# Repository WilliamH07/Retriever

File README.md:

<div align="center">

# Retriever

**Open source autonomous outdoor mobile robot**

[Architecture](docs/architecture/) ·
[Getting started](docs/DEMARRAGE.md) ·
[Bench reports](docs/bancs/) ·
[Hardware](hardware/) ·
[Support the project](#supporting-the-project)

</div>

---

## What this is

Retriever is a four wheel drive outdoor robot, built by one person and released
as open hardware. Its single objective is autonomous outdoor navigation with
ROS 2 Jazzy and Nav2, on a chassis anyone can reproduce from documented,
commodity parts.

It is an open rebuild inspired by the [Clearpath
Husky](https://clearpathrobotics.com/husky-a300-unmanned-ground-vehicle-robot/),
a reference platform in mobile robotics labs. The Husky is an excellent machine,
priced as a commercial product. Retriever asks a different question: how much of
that capability can one person reach from recovered and off the shelf parts, if
the engineering is done properly rather than cheaply?

The hardware is deliberately ordinary. The discipline applied to it is not: an
architecture dossier written before the first part was cut, a failure mode
analysis, a hardware safety chain no software can override, and a measurable
exit criterion at every stage.

## Status

<div align="center">

</div>

| Stage | Exit criterion | State |
|:-----:|----------------|-------|
| 1 | Architecture dossier and CAD complete | done |
| 2 | Chassis fabricated and assembled | done |
| 2b | First sensors published to ROS 2 over a transport agnostic link | done: [IMU](docs/bancs/imu.md) at 99.8 Hz, [lidar](docs/bancs/lidar.md) |
| 2c | Motor bench: hub motors driven from Foxglove | **current**: [coded, first spin due](docs/bancs/moteurs.md) |
| 3 | Three PCBs redesigned, power chain energised, no motor connected | **boards designed**: [KiCad, ERC and DRC clean](hardware/pcb/), fabrication next |
| 4 | Motors driven, wheels raised, all stop tests pass | planned |
| 5 | Autonomous outdoor navigation to a waypoint | planned |

Beyond stage 5, the plan is to mount a [Niryo
One](https://github.com/NiryoRobotics/niryo_one) arm and turn Retriever into a
mobile manipulator.

<div align="center">

</div>

## System architecture

<div align="center">

</div>

Three decisions shape everything else.

**A CAN bus, not USB, carries every command.** Four BLDC drivers chopping tens
of amps within 30 cm of the signal wiring make USB the wrong choice for the
control path: it is master slave, dynamically enumerated, with no frame
priority. CAN 2.0A at 500 kbit/s links the computer to every microcontroller.
USB is kept for high bandwidth perception, whose loss degrades the mission but
cannot cause dangerous motion. On the bench today the same frames travel over
serial; one Kconfig option and one launch parameter switch to CAN.

**The main computer never does real time.** It runs perception, localisation,
Nav2 and the mission, and produces setpoints. A dedicated safety
microcontroller decides whether they may be executed: the computer requests
arming, the safety node grants or refuses it.

**Safety is hardware, and independent of software.** Six stop levels, from a
100 ms software collision monitor down to a latching emergency stop and a
manual battery isolator. The last two contain no code at all.

<div align="center">

</div>

## Power

<div align="center">

</div>

The contactor is designed onto the power board rather than bought: a
`TPS48100-Q1` driving two opposed MOSFETs cuts a fault in 4.3 µs, draws 4 mW
instead of a coil's 2 to 8 W, and can test itself. The trade off is documented
in [`12-contacteur-statique.md`](docs/architecture/12-contacteur-statique.md).

## Printed circuit boards

<div align="center">

</div>

| Board | Role | State |
|---|---|---|
| [`safety_bus_distribution`](hardware/pcb/safety_bus_distribution/) | CAN and `/SAFE` trunk, protected 5 V per node, no microcontroller | **v2.0, ready to order** |
| [`motor_interface`](hardware/pcb/motor_interface/) | Hall tap and command path between a MOTION ESP32 and two ZS-X11H drivers | v2.0 draft, waits for motor measurements |
| [`safety_power`](hardware/pcb/safety_power/) | Battery input, static contactor, precharge, brake chopper, rails, SAFETY ESP32 | v2.0 draft, waits for pack measurements and an expert review |

Each board is described once, in a Python script that generates both the KiCad 10
schematic and the layout, so the two cannot drift apart. ERC, DRC and schematic
parity are all at zero, and the Gerber, BOM and placement files are committed.
The analogue blocks were simulated with ngspice, which caught one defect before
anything was ordered ([simulations](hardware/pcb/simulations.md)). None of the
boards has been built yet: [status of all three](hardware/pcb/etat-des-lieux.md)
(French).

## Hardware at a glance

| | |
|---|---|
| Configuration | 4WD skid steer, outdoor |
| Structure | Aluminium extrusion frame, laser cut panels, 3D printed mounts |
| Target mass | 35 kg in running order |
| Target speed | 1.5 m/s, slopes up to 10 % |
| Drivetrain | 4 × 6.5 inch hoverboard hub motors, 250 W each, 15 pole pairs |
| Motor drivers | 4 × ZS-X11H BLDC drivers, two per motor node |
| Battery | Xiaomi M365 Pro pack, 10S4P, 37 V nominal (30 to 42 V), 474 Wh |
| Endurance | about 2 h at 200 W average (estimate, 85 % depth of discharge) |
| Compute | Youyeetoo X1 (Celeron N5105), Ubuntu 24.04, ROS 2 Jazzy |
| Real time | 3 × ESP32 (SAFETY, MOTION front, MOTION rear) on CAN 2.0A, 500 kbit/s |
| Sensors | BNO085 IMU (SPI), YDLIDAR X4, GNSS; outdoor lidar and depth camera wanted |
| Localisation | GNSS, IMU and wheel odometry, dual EKF |
| Navigation | Nav2, collision monitor, twist mux |

## Repository layout

```
docs/
  architecture/   the design dossier: 00–07 base, 08–12 PCB and errata, 13 software
  bancs/          bench reports: IMU, lidar, motors (French)
  DEMARRAGE.md    getting started, from a blank machine to /imu/data (French)
  measurements/   bench measurements that gate the hardware design
  foxglove/       Foxglove Studio layouts for each bench
  images/         renders, build photos, diagrams
  sponsorship/    the sponsorship dossier
  archive/        superseded work, kept for history
hardware/
  icd.yaml        interface control document: every connector, every pin
  pcb/            three boards, generated from Python into KiCad 10, with fab files
  cad/            laser cut DXF profiles, mechanical notes
  bom/            pointer to the costed bill of materials
firmware/
  protocol/       protocol.yaml, the single source of truth, and its generator
  components/     link layer, protocol header, BNO085 driver
  esp32_safety/   safety node (IMU bench today)
  esp32_motion/   motor node, front and rear
  test/           host tests, no hardware needed
ros2_ws/src/
  retriever_link/       transport agnostic bridge: serial today, SocketCAN later
  retriever_protocol/   generated protocol header for ROS 2
  retriever_msgs/       message definitions
  retriever_bringup/    launch files and bench configurations
  retriever_*           description, hardware, control, navigation, teleop: planned
tools/            bench scripts, flashing, protocol and link checks
```

## Documentation

The design documentation is in French; an English summary is planned. Every
claim carries a marker: verified against a datasheet, community consensus, to
be measured, or an explicit assumption.

| Start with | Why |
|---|---|
| [Documentation index](docs/README.md) | One page that says what each document is for and whether it is current |
| [Démarrage](docs/DEMARRAGE.md) | Install, flash an ESP32, build the workspace, verify the IMU chain stage by stage |
| [Bench reports](docs/bancs/) | What runs today, with measured numbers, and the silent defects found on the way |
| [Architecture dossier](docs/architecture/) | Power, communications, ROS 2, safety, network, BOM and FMEA, operator console |
| [Corrections v1.2](docs/architecture/11-corrections-v1.2.md) | Takes precedence over 00–07 wherever they disagree |

## Supporting the project

Retriever is self funded by a student. Four items stand between the current
platform and autonomous outdoor operation:

- **Printed circuit boards.** Three boards are designed and checked: a motor
  interface, a safety and power board, and a passive CAN and safety bus
  distribution board. Fabrication is the next step.
- **Embedded AI compute.** The current x86 board runs the navigation stack, but
  not the perception outdoor autonomy asks for.
- **An outdoor lidar.** The blocking item. The 2D lidar on hand is specified for
  indoor use, and direct sunlight saturates its receiver.
- **A depth camera.** The Kinect v2 on hand is blind in daylight and its driver
  has been unmaintained since 2021.

Sponsors get a written and filmed integration tutorial for the sponsored part,
a field test video with honest performance data, attribution on the chassis and
here, and private feedback on how the part behaves on a real robot before
anything is published.

The full dossier is in [docs/sponsorship](docs/sponsorship/). Enquiries welcome:
see contact below.

## Credits

Inspired by the Clearpath Husky platform. The mechanical design was modelled
from scratch and the electrical and software architecture designed
independently. Some ROS 2 package conventions follow the open source
[husky/husky](https://github.com/husky/husky) repository, published under BSD 3
Clause. Clearpath Robotics is not affiliated with this project and does not
endorse it.

See [CREDITS.md](CREDITS.md) for the full attribution, and
[CONTRIBUTING.md](CONTRIBUTING.md) before opening a pull request.

## Licence

Software and firmware are released under the [Apache License 2.0](LICENSE).
Hardware designs, CAD and PCB files are released under the [CERN Open Hardware
Licence Version 2, Strongly Reciprocal](LICENSE-HARDWARE.txt).

## Contact

William Hanczyk, Bordeaux, France
wcontact33@gmail.com

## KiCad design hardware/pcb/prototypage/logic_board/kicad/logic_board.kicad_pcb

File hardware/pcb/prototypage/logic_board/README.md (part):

# logic_board — v1.0-draft (option B)

> **v1.0-draft — NE PAS FABRIQUER before P1, coil voltage, BMS level, and a review by an
> electronics engineer.**

Option B of the PCBWay comparison. Option A is [`../mainboard/`](../mainboard/): one big
board that also carries the 30 A motor power. It is left unchanged. This board keeps every
circuit whose parts are too small to solder by hand, so PCBWay can assemble it. The 30 A
path and the isolated 12 V PC converter move off board, onto wires, bus bars and
off-the-shelf fuse holders.

> ⚠️ **Routing is not finished.** The autorouted board still has **48 unconnected items**
> (31 signal connections and 17 cut-off pieces of the GND pours) and 12 dangling-track
> warnings. ERC is 0 and schematic parity is 0, placement and footprints are final, but the
> Gerbers in `fab/` are **for review and quoting only**: they must not be ordered until the
> remaining connections are finished by hand in KiCad (or the board goes to 4 layers).
> Details: [`decisions.md`](decisions.md) §3 (L11, L14) and §9.

## A or B: comparison

All money figures are **estimates, not a quote**: get an online PCBWay quote with each
`fab/` folder before deciding. Method and assumptions: [`decisions.md`](decisions.md) §8
and [`../mainboard/decisions.md`](../mainboard/decisions.md) §10.

| | A: `mainboard` | B: `logic_board` (this board) |
|---|---|---|
| PCB | 180 × 150 mm, 2 layers, **2 oz**, 1.6 mm | **100 × 140 mm**, 2 layers, **1 oz**, 1.6 mm |
| Board area | 270 cm² | 140 cm² (52 % of A) |
| Placed by PCBWay (`--fine-only`) | 192 parts, ≈ 496 pads | 190 parts, ≈ 492 pads |
| Unique machine-placed BOM lines | 50 | 49 |
| Full-SMD alternative (all SMD by PCBWay) | 273 parts / 78 lines | 267 parts / 74 lines |
| Soldered by William on the board | 120 (39 through-hole + 81 larger SMD) | 105 (28 through-hole + 77 larger SMD) |
| PCB, 5 boards | 40–80 € | 10–30 € (above the 100 × 100 price tier) |
| Assembly of 1 board (setup, stencil, ≈ 500 joints) | 30–80 € | 30–80 € |
| Fine SMD parts for 1 board | 30–50 € | 30–50 € (same ICs) |
| Shipping to France | 20–35 € | 20–35 € |
| **PCBWay order total** | **≈ 120–245 €** | **≈ 90–190 €** |
| Parts William buys that only this option needs | XT30, 4 × Keystone 3568, 5 A NANO2, M4/M5 bolts and lugs, 12 V PC terminal block: ≈ 15–25 € | Off-board power distribution (table below): ≈ 60–140 € |
| Parts William buys in both | larger SMD parts, connectors, sockets, IRL540N ×2, 10 Ω 5 W, 2200 µF, URB 12 V PC module (25–35 €), 22 Ω 100 W resistor, wires to the drivers, 3 DevKitC | same |
| Power wires (ends to crimp or bolt) | 16 | ≈ 24 (+ 8 inline fuse holders) |
| Signal connectors to plug | 18 | 20 (adds the power entry `J1` and the shunt Kelvin pair `J2`) |
| Battery connector | **XT30 on the board: 15 A continuous limit**, firmware cap 13 A | free choice on a wire: **XT60 proposed, no 15 A limit** (William's call) |
| 30 A copper | on the PCB, 2 oz, IPC-2152 approximation not checked by measurement | none on the PCB; 12 AWG wires and bus bars |
| Main safety risks | XT30 heating if the firmware limit fails; hot spot on the BUS_P neck | more bolted/crimped joints in the 30 A path (workmanship); fuse holder housings marked 32 V; Kelvin sense wires at bus potential without fuses |

**What the table says.** The machine-placed part count is the same: every small part is
on both boards. B saves on the bare PCB (smaller, 1 oz), so the PCBWay order is about
30–55 € cheaper, but William pays ≈ 35–115 € more for the off-board distribution (≈ 60–140 € of B-only parts minus ≈ 15–25 € of A-only parts) and has
more wiring to do. If the sponsorship covers only the PCBWay order, B moves cost from
PCBWay to William; neither option fits in 60 €. B's real gain is technical: no 30 A on
the PCB and no XT30 limit.

## What stays on the board

- The three **ESP32-DevKitC V4** on sockets (SAFETY, MOTION AVANT, MOTION ARRIÈRE): they
  are the wiring hub. CAN between them on traces (3 × `TCAN1042HVDR`, 120 Ω, XH to the
  CANable).
- **Power entry `J1`** (JST VH 5-pin): 1 BAT_F (fused 7.5 A off board), 2 GND, 3 BUS (fused
  7.5 A), 4 CHOP_N (from the chopper resistor), 5 GND. Input TVS `SMCJ48CA`.
- **5 V and 12 V AUX** (`TPS54360B` ×2, mainboard values), reverse-polarity FET,
  `5V_BRAKE` reservoir.
- **Precharge** (P-FET `SUD50P10-43L`, 10 Ω 5 W resistor standing up), output to the bus
  through `J1`-3.
- **Brake chopper**: analog control (`TPS7A4001`, `TLV1701`, `LM4040`, 0.1 % divider,
  `UCC27517`) and the `IRL540N`; the 22 Ω / 100 W resistor is off board.
- **Contactor coil** driver (`SN74AHCT1G08` → `IRL540N`), coil supply jumper, E-stop loops.
- **Safety chain**: `/SAFE`, watchdog latch (`TPL5010` → `74LVC1G74`).
- `INA228` with a Kelvin connector (`J2`) to the **off-board shunt**; VBAT and VBUS
  dividers.
- Hall taps, VR/DIR/STOP/EL for the four ZS-X11H, all JST XH driver connectors.
- IMU socket (1×10, BNO085 breakout order) and BMS JST GH.

GPIO tables are those of the mainboard (`../mainboard/decisions.md` §7), unchanged; the IMU
is wired as `firmware/esp32_safety/main/board_config.h`.

## Off-board power distribution

**Never route 30 A on perfboard.** The 30 A path is 12 AWG wire, crimped ring terminals,
two bus bars and inline fuse holders.

Ordinary blade fuses (ATO/ATC/MINI) are rated **32 V DC: do not use them on the 42 V
battery.** Littelfuse makes a **MINI 58 V** series (`0997`, 2–30 A, 1000 A breaking at
58 V DC) that fits MINI holders; the Littelfuse MINI FHM inline holder is listed as
compatible with both 32 V and 58 V MINI fuses (its housing is marked 32 V: see
"Not verified"). I found no ready-made fuse block rated ≥ 58 V DC at hobby prices.

```
                     12 AWG (30 A)                              18 AWG (≤ 7.5 A)
 BATTERY + ──XT60──[ BREAKER ]──● BAT+ (contactor battery terminal)
                                │
                                ├──[F5 7.5 A]──────────────────► J1-1 BAT_F   (logic board)
                                ├──[F8 3 A]────────────────────► 12 V PC module (+ in)
                                │
                         [ CONTACTOR ]   coil: J13; E-stop NC contact in series: J11
                                │
                         [ SHUNT 50 A / 75 mV ]──Kelvin screws──► J2-1 SNS_P, J2-2 SNS_N (twisted)
                                │
                    ════ BUS+ BAR ════
                      │    │    │    │    │
                   [F1] [F2] [F3] [F4] [F6 7.5 A]───────────────► J1-3 BUS
                    25A  25A  25A  25A   │
                      │    │    │    │  [F7 5 A]──[ 22 Ω 100 W ]──► J1-4 CHOP_N
                   AV_G AV_D AR_G AR_D   (ZS-X11H power +)
                      │    │    │    │
 BATTERY − ──XT60── ════ GND BAR ════ ─────────────────────────► J1-2 and J1-5 GND
                                └──► 12 V PC module (− in); isolated 12 V out → PC
```

Rules: every wire leaving a bus bar goes through its fuse first, mounted close to the bar;
crimp (do not only solder) ring terminals; the GND bar is the single star point (the
negative is never switched).

### What William buys for option B (estimates)

| # | Part | Qty | Estimate |
|---|---|---|---|
| 1 | XT60 pair (male + female), or keep an XT30 pair with the 15 A limit | 1 | 1–3 € |
| 2 | Bus bar, 4–6 studs, ≥ 100 A (one BUS+, one GND) | 2 | 10–24 € |
| 3 | DC shunt 50 A / 75 mV (1.5 mΩ, FL-2 type) | 1 | 3–8 € |
| 4 | Littelfuse MINI FHM inline holder, 12 AWG, 30 A (`0FHM0002ZXJ`), for F1–F4 | 4 | 12–32 € |
| 5 | Littelfuse MINI FHM inline holder, 14 AWG, 20 A (`0FHM0001ZXJ`), for F5–F8 | 4 | 10–25 € |
| 6 | MINI 58 V fuses: 4 × 25 A (`0997025.WXN`), 2 × 7.5 A, 1 × 5 A, 1 × 3 A (`0997` series), + spares | 8+ | 4–10 € |
| 7 | Silicone wire 12 AWG red/black (2 m each), 18 AWG (3 m), 24 AWG twisted pair | — | 10–20 € |
| 8 | Ring terminals M5/M6, heat-shrink, sleeving for the Kelvin pair | — | 5–10 € |
| 9 | JST VH 5-pin housing + crimps (`VHR-5N`, `SVH-21T-P1.1`), XH 2-pin housing | 1 | 1–3 € |
| 10 | Small perfboard + 2 screw terminals for the URB 12 V PC module (module itself counted in both options) | 1 | 2–4 € |
| | **Total** | | **≈ 60–140 €** |

Lead times: Littelfuse FHM holders showed long distributor lead times (weeks) when
checked; order early or ask for an equivalent holder rated for 58 V MINI fuses.

## Status

v1.0-draft, generated by `scripts/build.py` (KiCad 10), checked with `kicad-cli` on
24 Nov 2026:

| | |
|---|---|
| Size | 100 × 140 mm, 2 layers, **1 oz**, 1.6 mm, 4 × M3 holes |
| ERC | 0 |
| DRC (all severities, schematic parity) | **not clean**: 48 unconnected items (31 signal, 17 GND pour pieces), 12 `track_dangling` warnings, 0 other violations, 0 parity issues |
| Vias | 852 (183 GND fan-out vias placed before routing, stitching and joining vias) |
| Parts | 311 schematic symbols; `--fine-only`: 190 placed by PCBWay, 105 by hand, 102 BOM lines |
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
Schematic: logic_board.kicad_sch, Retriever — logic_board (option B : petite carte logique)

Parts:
C1, C2, C16: 2.2µF 100V; C_1210_3225Metric; MPN FS32X225K101EGG; LCSC C153036
C3, C11, C13, C22, C23, C24, C25, C31, C32, C33, C34, C102, C103, C104, C120, C130, C202, C203, C204, C220, C230, C305, C325, C345, C365: 100nF; C_0603_1608Metric; MPN CC0603KRX7R9BB104; LCSC C14663
C9: 1µF 100V; C_0805_2012Metric; MPN HMK212BC7105KGHTE; LCSC C385977
C10, C18, C21, C101, C201: 10µF 25V; C_0805_2012Metric; MPN CL21A106KAYNNNE; LCSC C15850
C12: 1nF; C_0603_1608Metric; MPN CL10B102KB8NNNC; LCSC C1588
C14, C30: 1µF 50V; C_0603_1608Metric; MPN CL10A105KB8NNNC; LCSC C15849
C15: 47µF 100V; CP_Elec_8x10; MPN RV100V47M8X10; LCSC C48935391
C17: 2200µF 10V; CP_Radial_D10.0mm_P5.00mm; MPN ERA10V2200M10X16; LCSC C49256788
C300, C301, C302, C320, C321, C322, C340, C341, C342, C360, C361, C362: 10nF 100V; C_0603_1608Metric; MPN 0603B103K101NT; LCSC C43253
CB51, CB52, CB121, CB122: 2.2µF 100V; C_1210_3225Metric; MPN FS32X225K101EGG; LCSC C153036
CB53, CB123: 100nF 100V; C_0603_1608Metric; MPN 0603B104K101NT; LCSC C88219
CB54, CB124: 100nF; C_0603_1608Metric; MPN CC0603KRX7R9BB104; LCSC C14663
CB55: 8.2nF; C_0603_1608Metric; MPN 0603B822K500NT; LCSC C1322360
CB56, CB126: 82pF C0G; C_0603_1608Metric; MPN CC0603JRNPO9BN820; LCSC C107056
CB57, CB58, CB59: 47µF 10V; C_1210_3225Metric; MPN GRM32ER71A476KE15L; LCSC C84494
CB125: 15nF; C_0603_1608Metric; MPN CC0603KRX7R9BB153; LCSC C107076
CB127, CB128, CB129: 22µF 25V; C_1210_3225Metric; MPN CL32A226KAJNNNE; LCSC C52306
D1: SMCJ48CA; D_SMC; MPN SMCJ48CA; LCSC C151287
D2, D12: BZT52C12; D_SOD-123; MPN BZT52C12; LCSC C43491
D3, D8: SS510C; D_SMC; MPN SS510C; LCSC C19229
D9: LM4040A25; SOT-23; MPN LM4040A25IDBZR; LCSC C9421
D10: CHOP; LED_0603_1608Metric; MPN KT-0603R; LCSC C2286
D11: BUS LIVE; LED_0603_1608Metric; MPN KT-0603R; LCSC C2286
D13: 5V; LED_0603_1608Metric; MPN 19-217/GHC-YR1S2/3T; LCSC C72043
D14: SS34; D_SMA; MPN SS34; LCSC C8678
D16, D101, D201: B5819W; D_SOD-123; MPN B5819W; LCSC C8598
D19: NUP2105L; SOT-23; MPN NUP2105LT1G; LCSC C14486
D20: ESD5Z3.3; D_SOD-523; MPN ESD5Z3.3T1G; LCSC C397781
D21: S1M; D_SMA; MPN S1M; LCSC C2128
D22, D23, D300, D301, D302, D320, D321, D322, D340, D341, D342, D360, D361, D362: BAT54S; SOT-23; MPN BAT54S,215; LCSC C47546
DB5, DB12: B560C; D_SMC; MPN B560C-13-F; LCSC C85100
J1: PUISSANCE; JST_VH_B5P-VH_1x05_P3.96mm_Vertical; MPN B5P-VH(LF)(SN)
J2: SHUNT KELVIN; JST_XH_B2B-XH-A_1x02_P2.50mm_Vertical; MPN B2B-XH-A(LF)(SN); LCSC C158012
J8: FAN 12V; JST_XH_B2B-XH-A_1x02_P2.50mm_Vertical; MPN B2B-XH-A(LF)(SN); LCSC C158012
J9: CAN PC; JST_XH_B3B-XH-A_1x03_P2.50mm_Vertical; MPN B3B-XH-A(LF)(SN); LCSC C144394
J10: ARU /SAFE (NF); JST_XH_B2B-XH-A_1x02_P2.50mm_Vertical; MPN B2B-XH-A(LF)(SN); LCSC C158012
J11: ARU BOBINE (NF); JST_XH_B2B-XH-A_1x02_P2.50mm_Vertical; MPN B2B-XH-A(LF)(SN); LCSC C158012
J13: BOBINE CONTACTEUR; JST_XH_B2B-XH-A_1x02_P2.50mm_Vertical; MPN B2B-XH-A(LF)(SN); LCSC C158012
J14: IMU BNO085; PinSocket_1x10_P2.54mm_Vertical; MPN 1x10 female header 2.54 mm
J15: BMS; JST_GH_SM04B-GHS-TB_1x04-1MP_P1.25mm_Horizontal; MPN SM04B-GHS-TB(LF)(SN); LCSC C189895
JC1: COMMANDE AV_G; JST_XH_B6B-XH-A_1x06_P2.50mm_Vertical; MPN B6B-XH-A(LF)(SN); LCSC C157992
JC2: COMMANDE AV_D; JST_XH_B6B-XH-A_1x06_P2.50mm_Vertical; MPN B6B-XH-A(LF)(SN); LCSC C157992
JC3: COMMANDE AR_G; JST_XH_B6B-XH-A_1x06_P2.50mm_Vertical; MPN B6B-XH-A(LF)(SN); LCSC C157992
JC4: COMMANDE AR_D; JST_XH_B6B-XH-A_1x06_P2.50mm_Vertical; MPN B6B-XH-A(LF)(SN); LCSC C157992
JD1: HALL VARIATEUR AV_G; JST_XH_B5B-XH-A_1x05_P2.50mm_Vertical; MPN B5B-XH-A(LF)(SN); LCSC C157991
JD2: HALL VARIATEUR AV_D; JST_XH_B5B-XH-A_1x05_P2.50mm_Vertical; MPN B5B-XH-A(LF)(SN); LCSC C157991
JD3: HALL VARIATEUR AR_G; JST_XH_B5B-XH-A_1x05_P2.50mm_Vertical; MPN B5B-XH-A(LF)(SN); LCSC C157991
JD4: HALL VARIATEUR AR_D; JST_XH_B5B-XH-A_1x05_P2.50mm_Vertical; MPN B5B-XH-A(LF)(SN); LCSC C157991
JM1: HALL MOTEUR AV_G; JST_XH_B5B-XH-A_1x05_P2.50mm_Vertical; MPN B5B-XH-A(LF)(SN); LCSC C157991
JM2: HALL MOTEUR AV_D; JST_XH_B5B-XH-A_1x05_P2.50mm_Vertical; MPN B5B-XH-A(LF)(SN); LCSC C157991
JM3: HALL MOTEUR AR_G; JST_XH_B5B-XH-A_1x05_P2.50mm_Vertical; MPN B5B-XH-A(LF)(SN); LCSC C157991
JM4: HALL MOTEUR AR_D; JST_XH_B5B-XH-A_1x05_P2.50mm_Vertical; MPN B5B-XH-A(LF)(SN); LCSC C157991
JP1: BOBINE 12V|BAT; PinHeader_1x03_P2.54mm_Vertical; MPN 1x3 pin header 2.54 mm + 1 jumper shunt
LB5: 15µH; L_TaiTech_TMPC1265_13.5x12.5mm; MPN SRP1265A-150M; LCSC C189912
LB12: 33µH; L_TaiTech_TMPC1265_13.5x12.5mm; MPN MDA1365-330M; LCSC C2847586
Q3, Q6: SUD50P10-43L; TO-252-2; MPN SUD50P10-43L-TP; LCSC C41408040
Q4: MMBT5551; SOT-23; MPN MMBT5551; LCSC C2145
Q5, Q10: IRL540N; TO-220-3_Vertical; MPN IRL540NPBF
Q8, Q9, Q120, Q121, Q122, Q130, Q131, Q132, Q220, Q221, Q222, Q230, Q231, Q232: AO3400A; SOT-23; MPN AO3400A; LCSC C20917
R1, R2, R19, R29: 10Ω; R_0603_1608Metric; MPN 0603WAF100JT5E; LCSC C22859
R3, R21, R22, R28, R42, R49, R51, R56, R57, R61, R66, R101, R105, R109, R124, R134, R201, R205, R209, R224, R234: 10k; R_0603_1608Metric; MPN 0603WAF1002T5E; LCSC C25804
R4: 22k; R_0603_1608Metric; MPN 0603WAF2202T5E; LCSC C31850
R5, R33: 4.7k; R_0603_1608Metric; MPN 0603WAF4701T5E; LCSC C23162
R6, R30, R31, R35, R45, R46, R47, R64, R103, R106, R110, R120, R121, R122, R130, R131, R132, R203, R206, R210, R220, R221, R222, R230, R231, R232: 100k; R_0603_1608Metric; MPN 0603WAF1003T5E; LCSC C25803
R7: 10Ω 5W; R_Axial_Power_L25.0mm_W9.0mm_P10.16mm_Vertical; MPN SQP500JB-10R
R20: 93.1k; R_0603_1608Metric; MPN AC0603FR-0793K1L; LCSC C228101
R23, R24: 49.9k 0.1%; R_0603_1608Metric; MPN AR03BTCX4992; LCSC C2828622
R25: 6.19k 0.1%; R_0603_1608Metric; MPN TD03G6191BT; LCSC C667011
R26: 0R; R_0603_1608Metric; MPN 0603WAF0000T5E; LCSC C21189
R27: 1.69M; R_0603_1608Metric; MPN 0603WAF1694T5E; LCSC C247054
R32: 33k; R_0603_1608Metric; MPN 0603WAF3302T5E; LCSC C4216
R34: 22k; R_1206_3216Metric; MPN RC1206FR-0722KL; LCSC C114942
R36, R55, R59, R65: 1k; R_0603_1608Metric; MPN 0603WAF1001T5E; LCSC C21190
R37, R38, R39, R40: 220Ω; R_1206_3216Metric; MPN 1206W4F2200T5E; LCSC C17958
R43, R44, R300, R301, R303, R304, R306, R307, R320, R321, R323, R324, R326, R327, R340, R341, R343, R344, R346, R347, R360, R361, R363, R364, R366, R367: 2.2k; R_0603_1608Metric; MPN 0603WAF2201T5E; LCSC C4190
R48, R50: 243k; R_0603_1608Metric; MPN 0603WAF2433T5E; LCSC C23351
R52: 120Ω; R_0603_1608Metric; MPN 0603WAF1200T5E; LCSC C22787
R60: 5.23k; R_0603_1608Metric; MPN 0603WAF5231T5E; LCSC C23068
R62, R63, R68, R123, R133, R223, R233: 100Ω; R_0603_1608Metric; MPN 0603WAF1000T5E; LCSC C22775
R67: 22k; R_0603_1608Metric; MPN 0603WAF2202T5E; LCSC C31850; not fitted
R102, R202: 47k; R_0603_1608Metric; MPN 0603WAF4702T5E; LCSC C25819
R104, R108, R204, R208: 6.8k; R_0603_1608Metric; MPN 0603WAF6801T5E; LCSC C23212
RB51, RB121: 1.18M; R_0603_1608Metric; MPN AA0603FR-071M18L; LCSC C4072929
RB52, RB122: 59k; R_0603_1608Metric; MPN 0603WAF5902T5E; LCSC C23085
RB53, RB123: 243k; R_0603_1608Metric; MPN 0603WAF2433T5E; LCSC C23351
RB54: 53.6k; R_0603_1608Metric; MPN 0603WAF5362T5E; LCSC C23074
RB55, RB125: 10.2k; R_0603_1608Metric; MPN 0603WAF1022T5E; LCSC C22772
RB56: 10.7k; R_0603_1608Metric; MPN 0603WAF1072T5E; LCSC C22857
RB124: 143k; R_0603_1608Metric; MPN RS-03K1433FT; LCSC C304703
RB126: 10.5k; R_0603_1608Metric; MPN 0603WAF1052T5E; LCSC C22855
TP1: 5V; TestPoint_Pad_D1.5mm
TP2: 3V3_S; TestPoint_Pad_D1.5mm
TP3: SAFE_N; TestPoint_Pad_D1.5mm
TP4: TRIP_N; TestPoint_Pad_D1.5mm
TP5: LATCH_Q; TestPoint_Pad_D1.5mm
TP6: CANH; TestPoint_Pad_D1.5mm
TP7: CANL; TestPoint_Pad_D1.5mm
TP8, TP12: GND; TestPoint_Pad_D1.5mm
TP9: CH_12V; TestPoint_Pad_D1.5mm
TP10: CH_CMD; TestPoint_Pad_D1.5mm
TP11: CHOP_ACT; TestPoint_Pad_D1.5mm
TP13: 12V_AUX; TestPoint_Pad_D1.5mm
TP14: 3V3_AV; TestPoint_Pad_D1.5mm
TP15: 3V3_AR; TestPoint_Pad_D1.5mm
U1: INA228; TSSOP-10_3x3mm_P0.5mm; MPN INA228AIDGSR; LCSC C2887910
U3: TPS7A4001; HVSSOP-8-1EP_3x3mm_P0.65mm_EP1.57x1.89mm_Pad0.42; MPN TPS7A4001DGNT; LCSC C5144143
U4: TLV1701; SOT-23-5; MPN TLV1701AIDBVR; LCSC C130035
U5: UCC27517; SOT-23-5; MPN UCC27517DBVR; LCSC C99395
U10: ESP32 SAFETY; ESP32-DevKitC-V4_Sockets_OpenCenter; MPN 2x 1x19 female socket 2.54 mm (e.g. Mil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
U11, U101, U201: TCAN1042HVDR; SOIC-8_3.9x4.9mm_P1.27mm; MPN TCAN1042HVDR; LCSC C127869
U14: TPL5010; SOT-23-6; MPN TPL5010DDCR; LCSC C473912
U15: SN74LVC1G74DCT; SSOP-8_2.95x2.8mm_P0.65mm; MPN SN74LVC1G74DCTR
U16: SN74AHCT1G08DBV; SOT-23-5; MPN SN74AHCT1G08DBVR
U20: ESP32 MOTION_AV; ESP32-DevKitC-V4_Sockets_OpenCenter; MPN 2x 1x19 female socket 2.54 mm (e.g. Mil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
U30: ESP32 MOTION_AR; ESP32-DevKitC-V4_Sockets_OpenCenter; MPN 2x 1x19 female socket 2.54 mm (e.g. Mil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
U102, U202: TLV9062IDR; SOIC-8_3.9x4.9mm_P1.27mm; MPN TLV9062IDR; LCSC C398355
U120, U130, U220, U230: SN74LVC1G08DBV; SOT-23-5; MPN SN74LVC1G08DBVR; LCSC C7666
U300, U320, U340, U360: SN74LVC3G17DCT; SSOP-8_2.95x2.8mm_P0.65mm; MPN SN74LVC3G17DCTR
UB5, UB12: TPS54360BDDAR; TI_SO-PowerPAD-8_ThermalVias; MPN TPS54360BDDAR; LCSC C524806

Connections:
/3V3_AR: C203.1, C220.1, C230.1, C345.1, C365.1, R201.2, TP15.1, U30.1 (3V3), U201.5 (VIO), U220.5 (VCC), U230.5 (VCC), U340.8 (VCC), U360.8 (VCC)
/3V3_AV: C103.1, C120.1, C130.1, C305.1, C325.1, R101.2, TP14.1, U20.1 (3V3), U101.5 (VIO), U120.5 (VCC), U130.5 (VCC), U300.8 (VCC), U320.8 (VCC)
/3V3_S: C3.1, C25.1, C31.1, C32.1, C34.1, D22.2 (K), D23.2 (K), J14.1, J14.9, R42.2, R43.2, R44.2, R55.1, R57.2, R61.2, R66.2, TP2.1, U1.6 (VS), U10.1 (3V3), U11.5 (VIO), U14.1 (VDD), U15.2 (D), U15.7 (~PRE), U15.8 (VCC)
/5V: C24.1, C33.1, C102.1, C104.1, C202.1, C204.1, CB57.1, CB58.1, CB59.1, D14.2 (A), D16.2 (A), D101.2 (A), D201.2 (A), LB5.2, R36.1, RB54.1, TP1.1, U11.3 (VCC), U16.5 (VCC), U101.3 (VCC), U102.8 (V+), U201.3 (VCC), U202.8 (V+)
/5V_AR: C201.1, D201.1 (K), U30.19 (5V)
/5V_AV: C101.1, D101.1 (K), U20.19 (5V)
/5V_BRAKE_M1: JC1.6, R37.2
/5V_BRAKE_M2: JC2.6, R38.2
/5V_BRAKE_M3: JC3.6, R39.2
/5V_BRAKE_M4: JC4.6, R40.2
/5V_MOT_M1: D300.2 (K), D301.2 (K), D302.2 (K), JD1.1, JM1.1, R300.1, R303.1, R306.1
/5V_MOT_M2: D320.2 (K), D321.2 (K), D322.2 (K), JD2.1, JM2.1, R320.1, R323.1, R326.1
/5V_MOT_M3: D340.2 (K), D341.2 (K), D342.2 (K), JD3.1, JM3.1, R340.1, R343.1, R346.1
/5V_MOT_M4: D360.2 (K), D361.2 (K), D362.2 (K), JD4.1, JM4.1, R360.1, R363.1, R366.1
/5V_S: C21.1, D16.1 (K), U10.19 (5V)
/12V_AUX: CB127.1, CB128.1, CB129.1, J8.1, JP1.1, LB12.2, RB124.1, TP13.1
/B5_BOOT: CB54.1, UB5.1 (BOOT)
/B5_COMP: CB56.1, RB56.1, UB5.6 (COMP)
/B5_CZ: CB55.1, RB56.2
/B5_EN: RB51.2, RB52.1, UB5.3 (EN)
/B5_FB: RB54.2, RB55.1, UB5.5 (FB)
/B5_RT: RB53.1, UB5.4 (RT/CLK)
/B5_SW: CB54.2, DB5.1 (K), LB5.1, UB5.8 (SW)
/B12_BOOT: CB124.1, UB12.1 (BOOT)
/B12_COMP: CB126.1, RB126.1, UB12.6 (COMP)
/B12_CZ: CB125.1, RB126.2
/B12_EN: RB121.2, RB122.1, UB12.3 (EN)
/B12_FB: RB124.2, RB125.1, UB12.5 (FB)
/B12_RT: RB123.1, UB12.4 (RT/CLK)
/B12_SW: CB124.2, DB12.1 (K), LB12.1, UB12.8 (SW)
/BAT_F: C1.1, C2.1, D1.1 (A1), D2.1 (K), J1.1, Q3.3 (S), Q6.2 (D), R3.2, R48.1
/BMS_R: J15.1, R65.1
/BMS_RX: D22.3 (COM), R65.2, R66.1, R67.1, U10.6 (IO35)
/BMS_T: J15.2, R68.2
/BMS_TX: D23.3 (COM), R68.1, U10.12 (IO14)
/BRAKE_REL_AR: R203.1, U30.22 (IO22), U220.1, U230.1
/BRAKE_REL_AV: R103.1, U20.22 (IO22), U120.1, U130.1
/BRK_RES: C17.1, C18.1, D14.1 (K), R37.1, R38.1, R39.1, R40.1
/BUS: D3.1 (K), D8.1 (K), J1.3, R19.1, R23.1, R34.1, R50.1
/CANH: D19.1 (K), J9.1, R52.1, TP6.1, U11.7 (CANH), U101.7 (CANH), U201.7 (CANH)
/CANL: D19.2 (K), J9.2, R52.2, TP7.1, U11.6 (CANL), U101.6 (CANL), U201.6 (CANL)
/CAN_RX_AR: U30.32 (IO4), U201.4 (RXD)
/CAN_RX_AV: U20.32 (IO4), U101.4 (RXD)
/CAN_RX_S: U10.32 (IO4), U11.4 (RXD)
/CAN_TX_AR: R201.1, U30.29 (IO5), U201.1 (TXD)
/CAN_TX_AV: R101.1, U20.29 (IO5), U101.1 (TXD)
/CAN_TX_S: R42.1, U10.29 (IO5), U11.1 (TXD)
/CHOP_ACT: R31.2, R32.1, TP11.1
/CHOP_N: D8.2 (A), J1.4, Q5.2 (D)
/CH_12V: C10.1, C13.1, C14.1, R20.1, R22.1, R28.1, TP9.1, U3.1 (OUT), U4.5 (V+), U5.1 (VDD)
/CH_B: R25.2, R26.1
/CH_CMD: R27.2, R28.2, R31.1, TP10.1, U4.4 (OUT), U5.3 (IN+)
/CH_DRV: R29.1, R33.1, U5.5 (OUT)
/CH_FB: R20.2, R21.1, U3.2 (FB)
/CH_G: Q5.1 (G), R29.2, R30.1
/CH_LED: D10.2 (A), R33.2
/CH_REF: C11.1, D9.1 (K), R22.2, U4.3 (IN-)
/CH_SNS: C12.1, R24.2, R25.1, R27.1, U4.1 (IN+)
/CH_T: R23.2, R24.1
/CH_VIN: C9.1, R19.2, U3.5 (EN), U3.8 (IN)
/COIL_EN: R47.1, U10.7 (IO32), U16.1
/COIL_G: Q10.1 (G), R63.2, R64.1
/COIL_GD: R63.1, U16.4
/COIL_N: D21.2 (A), J13.2, Q10.2 (D)
/COIL_P: D21.1 (K), J11.2, J13.1
/COIL_SUP: J11.1, JP1.2
/DAC1_AR: R206.1, U30.9 (IO25), U202.3 (+)
/DAC1_AV: R106.1, U20.9 (IO25), U102.3 (+)
/DAC2_AR: R210.1, U30.10 (IO26), U202.5 (+)
/DAC2_AV: R110.1, U20.10 (IO26), U102.5 (+)
/DIR1_AR: Q220.1 (G), R220.1, U30.11 (IO27)
/DIR1_AV: Q120.1 (G), R120.1, U20.11 (IO27)
/DIR2_AR: Q230.1 (G), R230.1, U30.12 (IO14)
/DIR2_AV: Q130.1 (G), R130.1, U20.12 (IO14)
/DIR_M1: JC1.2, Q120.3 (D)
/DIR_M2: JC2.2, Q130.3 (D)
/DIR_M3: JC3.2, Q220.3 (D)
/DIR_M4: JC4.2, Q230.3 (D)
/EL_M1: JC1.3, Q122.3 (D)
/EL_M1_G: Q122.1 (G), R122.1, U120.4
/EL_M2: JC2.3, Q132.3 (D)
/EL_M2_G: Q132.1 (G), R132.1, U130.4
/EL_M3: JC3.3, Q222.3 (D)
/EL_M3_G: Q222.1 (G), R222.1, U220.4
/EL_M4: JC4.3, Q232.3 (D)
/EL_M4_G: Q232.1 (G), R232.1, U230.4
/ESTOP1_A: J10.1, R55.2
/GND: C1.2, C2.2, C3.2, C9.2, C10.2, C11.2, C12.2, C13.2, C14.2, C15.2, C16.2, C17.2, C18.2, C21.2, C22.2, C23.2, C24.2, C25.2, C30.2, C31.2, C32.2, C33.2, C34.2, C101.2, C102.2, C103.2, C104.2, C120.2, C130.2, C201.2, C202.2, C203.2, C204.2, C220.2, C230.2, C300.2, C301.2, C302.2, C305.2, C320.2, C321.2, C322.2, C325.2, C340.2, C341.2, C342.2, C345.2, C360.2, C361.2, C362.2, C365.2, CB51.2, CB52.2, CB53.2, CB55.2, CB56.2, CB57.2, CB58.2, CB59.2, CB121.2, CB122.2, CB123.2, CB125.2, CB126.2, CB127.2, CB128.2, CB129.2, D1.2 (A2), D9.2 (A), D10.1 (K), D11.1 (K), D13.1 (K), D19.3 (A), D20.2 (A), D22.1 (A), D23.1 (A), D300.1 (A), D301.1 (A), D302.1 (A), D320.1 (A), D321.1 (A), D322.1 (A), D340.1 (A), D341.1 (A), D342.1 (A), D360.1 (A), D361.1 (A), D362.1 (A), DB5.2 (A), DB12.2 (A), J1.2, J1.5, J8.2, J9.3, J14.2, J15.3, JC1.5, JC2.5, JC3.5, JC4.5, JD1.2, JD2.2, JD3.2, JD4.2, JM1.2, JM2.2, JM3.2, JM4.2, Q4.2 (E), Q5.3 (S), Q8.2 (S), Q9.2 (S), Q10.3 (S), Q120.2 (S), Q121.2 (S), Q122.2 (S), Q130.2 (S), Q131.2 (S), Q132.2 (S), Q220.2 (S), Q221.2 (S), Q222.2 (S), Q230.2 (S), Q231.2 (S), Q232.2 (S), R6.2, R21.2, R26.2, R30.2, R32.2, R35.2, R45.2, R46.2, R47.2, R49.2, R51.2, R56.2, R60.2, R64.2, R67.2, R103.2, R105.2, R106.2, R109.2, R110.2, R120.2, R121.2, R122.2, R124.2, R130.2, R131.2, R132.2, R134.2, R203.2, R205.2, R206.2, R209.2, R210.2, R220.2, R221.2, R222.2, R224.2, R230.2, R231.2, R232.2, R234.2, RB52.2, RB53.2, RB55.2, RB122.2, RB123.2, RB125.2, TP8.1, TP12.1, U1.1 (A1), U1.2 (A0), U1.7 (GND), U3.4 (GND), U3.9 (PAD), U4.2 (V-), U5.2 (GND), U5.4 (IN-), U10.14 (GND), U10.20 (GND), U10.26 (GND), U11.2 (GND), U11.8 (STB), U14.2 (GND), U15.4 (GND), U16.3 (GND), U20.14 (GND), U20.20 (GND), U20.26 (GND), U30.14 (GND), U30.20 (GND), U30.26 (GND), U101.2 (GND), U101.8 (STB), U102.4 (V-), U120.3 (GND), U130.3 (GND), U201.2 (GND), U201.8 (STB), U202.4 (V-), U220.3 (GND), U230.3 (GND), U300.4 (GND), U320.4 (GND), U340.4 (GND), U360.4 (GND), UB5.7 (GND), UB5.9 (GNDPAD), UB12.7 (GND), UB12.9 (GNDPAD)
/HALL1_A_AR: U30.3 (IO36), U340.7
/HALL1_A_AV: U20.3 (IO36), U300.7
/HALL1_B_AR: U30.4 (IO39), U340.2
/HALL1_B_AV: U20.4 (IO39), U300.2
/HALL1_C_AR: U30.5 (IO34), U340.5
/HALL1_C_AV: U20.5 (IO34), U300.5
/HALL2_A_AR: U30.6 (IO35), U360.7
/HALL2_A_AV: U20.6 (IO35), U320.7
/HALL2_B_AR: U30.7 (IO32), U360.2
/HALL2_B_AV: U20.7 (IO32), U320.2
/HALL2_C_AR: U30.8 (IO33), U360.5
/HALL2_C_AV: U20.8 (IO33), U320.5
/HM1_A: JD1.3, JM1.3, R300.2, R301.1
/HM1_A_F: C300.1, D300.3 (COM), R301.2, U300.1
/HM1_B: JD1.4, JM1.4, R303.2, R304.1
/HM1_B_F: C301.1, D301.3 (COM), R304.2, U300.6
/HM1_C: JD1.5, JM1.5, R306.2, R307.1
/HM1_C_F: C302.1, D302.3 (COM), R307.2, U300.3
/HM2_A: JD2.3, JM2.3, R320.2, R321.1
/HM2_A_F: C320.1, D320.3 (COM), R321.2, U320.1
/HM2_B: JD2.4, JM2.4, R323.2, R324.1
/HM2_B_F: C321.1, D321.3 (COM), R324.2, U320.6
/HM2_C: JD2.5, JM2.5, R326.2, R327.1
/HM2_C_F: C322.1, D322.3 (COM), R327.2, U320.3
/HM3_A: JD3.3, JM3.3, R340.2, R341.1
/HM3_A_F: C340.1, D340.3 (COM), R341.2, U340.1
/HM3_B: JD3.4, JM3.4, R343.2, R344.1
/HM3_B_F: C341.1, D341.3 (COM), R344.2, U340.6
/HM3_C: JD3.5, JM3.5, R346.2, R347.1
/HM3_C_F: C342.1, D342.3 (COM), R347.2, U340.3
/HM4_A: JD4.3, JM4.3, R360.2, R361.1
/HM4_A_F: C360.1, D360.3 (COM), R361.2, U360.1
/HM4_B: JD4.4, JM4.4, R363.2, R364.1
/HM4_B_F: C361.1, D361.3 (COM), R364.2, U360.6
/HM4_C: JD4.5, JM4.5, R366.2, R367.1
/HM4_C_F: C362.1, D362.3 (COM), R367.2, U360.3
/HOTEL_IN: C15.1, C16.1, CB51.1, CB52.1, CB53.1, CB121.1, CB122.1, CB123.1, D12.1 (K), JP1.3, Q6.3 (S), RB51.1, RB121.1, UB5.2 (VIN), UB12.2 (VIN)
/I2C_SCL: R44.1, U1.5 (SCL), U10.33 (IO0)
/I2C_SDA: R43.1, U1.4 (SDA), U10.35 (IO15)
/IMU_CS: J14.6, U10.22 (IO22)
/IMU_INT: J14.7, U10.9 (IO25)
/IMU_MISO: J14.4, U10.27 (IO19)
/IMU_MOSI: J14.5, U10.21 (IO23)
/IMU_PS0: J14.10, U10.10 (IO26)
/IMU_RST: J14.8, U10.8 (IO33)
/IMU_SCK: J14.3, U10.28 (IO18)
/INA_N: R2.2, U1.8 (Vbus), U1.9 (Vin-)
/INA_P: R1.2, U1.10 (Vin+)
/LATCH_Q: TP5.1, U15.5 (Q), U16.2
/LATCH_QN: Q9.1 (G), U15.3 (~Q)
/LED_5V: D13.2 (A), R36.2
/LED_BUS: D11.2 (A), R34.2
/PRECH_EN: R5.1, U10.11 (IO27)
/PRE_B: Q4.1 (B), R5.2, R6.1
/PRE_C: Q4.3 (C), R4.2
/PRE_G: D2.2 (A), Q3.1 (G), R3.1, R4.1
/PRE_N: D3.2 (A), R7.2
/PRE_P: Q3.2 (D), R7.1
/REV_G: D12.2 (A), Q6.1 (G), R35.1
/SAFE_HOLD: Q8.1 (G), R57.1, U10.15 (IO13)
/SAFE_N: D20.1 (K), J10.2, Q8.3 (D), Q9.3 (D), R56.1, R59.1, R102.1, R202.1, TP3.1, U120.2, U130.2, U220.2, U230.2
/SAFE_N_IN_AR: R202.2, U30.27 (IO19)
/SAFE_N_IN_AV: R102.2, U20.27 (IO19)
/SAFE_N_IN_S: R59.2, U10.3 (IO36)
/SAFE_REARM: R46.1, U10.25 (IO21), U15.1 (CLK)
/SNS_N: J2.2, R2.1
/SNS_P: J2.1, R1.1
/STOP1_AR: Q221.1 (G), R221.1, U30.15 (IO13)
/STOP1_AV: Q121.1 (G), R121.1, U20.15 (IO13)
/STOP2_AR: Q231.1 (G), R231.1, U30.21 (IO23)
/STOP2_AV: Q131.1 (G), R131.1, U20.21 (IO23)
/STOP_M1: JC1.4, Q121.3 (D)
/STOP_M2: JC2.4, Q131.3 (D)
/STOP_M3: JC3.4, Q221.3 (D)
/STOP_M4: JC4.4, Q231.3 (D)
/TRIP_N: C30.1, R61.1, R62.2, TP4.1, U15.6 (~CLR)
/VBAT_ADC: C22.1, R48.2, R49.1, U10.4 (IO39)
/VBUS_ADC: C23.1, R50.2, R51.1, U10.5 (IO34)
/VR1_FB_AR: R204.2, R205.1, U202.2 (-)
/VR1_FB_AV: R104.2, R105.1, U102.2 (-)
/VR1_O_AR: R204.1, R223.1, U202.1
/VR1_O_AV: R104.1, R123.1, U102.1
/VR2_FB_AR: R208.2, R209.1, U202.6 (-)
/VR2_FB_AV: R108.2, R109.1, U102.6 (-)
/VR2_O_AR: R208.1, R233.1, U202.7
/VR2_O_AV: R108.1, R133.1, U102.7
/VR_M1: JC1.1, R123.2, R124.1
/VR_M2: JC2.1, R133.2, R134.1
/VR_M3: JC3.1, R223.2, R224.1
/VR_M4: JC4.1, R233.2, R234.1
/WD_DELAY: R60.1, U14.3 (DELAY/M_RST)
/WD_DONE: R45.1, U10.34 (IO2), U14.4 (DONE)
/WD_RST_N: R62.1, U14.6 (~RST)

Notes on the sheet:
1. ENTRÉE PUISSANCE (VH 5 broches depuis la distribution hors carte) — BAT_F fusible 7,5 A, BUS fusible 7,5 A, CHOP_N — TVS SMCJ48CA — INA228 sur shunt hors carte (prise Kelvin)
2. PRÉCHARGE — FET P SUD50P10-43L, NPN MMBT5551, 10 Ω 5 W debout sur la carte, diode série SS510C, sortie vers le bus par J1-3
3. HACHEUR DE FREINAGE (safety_power v2.1) — analogique, alimenté par le bus (J1-3), ON 43,0 V / OFF 42,3 V ; résistance 22 Ω 100 W hors carte entre le bus et J1-4
5. RAILS HÔTEL (amont contacteur, BAT_F fusible hors carte) — anti-inversion, 5 V et 12 V AUX (TPS54360B), 5V_BRAKE ; le 12 V PC isolé est un module hors carte
6. ESP32 SAFETY — CAN, /SAFE (pull-up 1 kΩ via l'arrêt d'urgence, pull-down 10 kΩ), verrou watchdog (D7), bobine du contacteur, IMU BNO085, BMS
7. ESP32 MOTION_AVANT — CAN, VR = DAC interne x 1,68 (TLV9062), DIR/STOP drain ouvert, EL = GPIO22 ET /SAFE
7. ESP32 MOTION_ARRIÈRE — CAN, VR = DAC interne x 1,68 (TLV9062), DIR/STOP drain ouvert, EL = GPIO22 ET /SAFE
8. MOTEUR M1 (AV_G) — passage Hall moteur→variateur, prélèvement 2,2 kΩ / 2,2 kΩ + 10 nF / BAT54S / SN74LVC3G17, commande VR DIR EL STOP + 5V_BRAKE
8. MOTEUR M2 (AV_D) — passage Hall moteur→variateur, prélèvement 2,2 kΩ / 2,2 kΩ + 10 nF / BAT54S / SN74LVC3G17, commande VR DIR EL STOP + 5V_BRAKE
8. MOTEUR M3 (AR_G) — passage Hall moteur→variateur, prélèvement 2,2 kΩ / 2,2 kΩ + 10 nF / BAT54S / SN74LVC3G17, commande VR DIR EL STOP + 5V_BRAKE
8. MOTEUR M4 (AR_D) — passage Hall moteur→variateur, prélèvement 2,2 kΩ / 2,2 kΩ + 10 nF / BAT54S / SN74LVC3G17, commande VR DIR EL STOP + 5V_BRAKE
v1.0-draft — ne pas fabriquer avant P1, coil voltage, BMS level, and a review by an electronics engineer

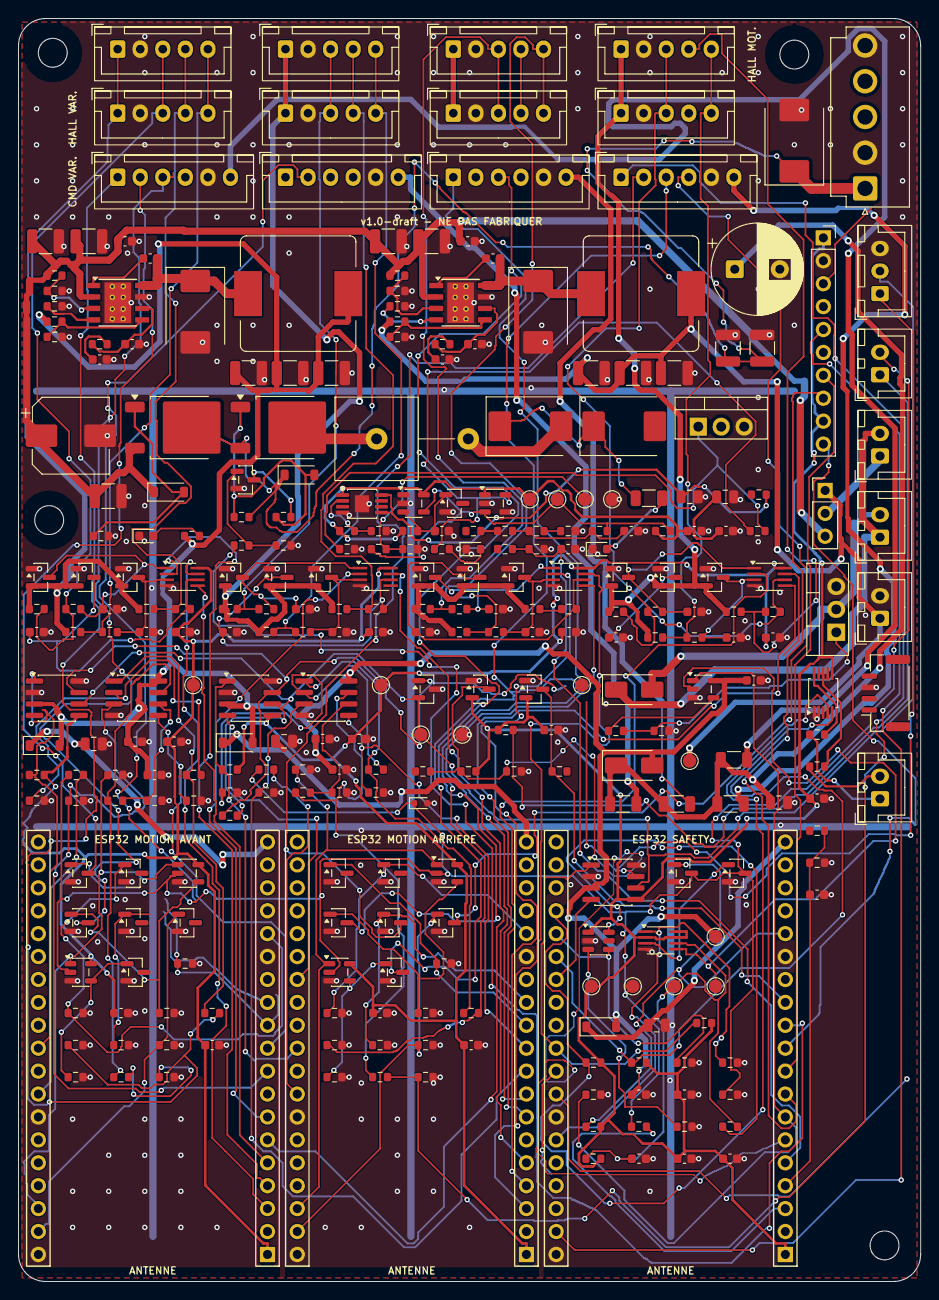
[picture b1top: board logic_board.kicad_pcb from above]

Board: 2 copper layers, 100.0 x 140.0 mm, 315 parts (0 on the bottom side), 181 nets.

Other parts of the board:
H1, H2, H3, H4: M3; MountingHole_3.2mm_M3

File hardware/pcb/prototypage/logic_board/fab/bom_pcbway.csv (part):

Item,Designator,Quantity,Manufacturer,MPN,Description,Package,Type,Placed by,LCSC (reference)
1,"C1,C2,C16,CB51,CB52,CB121,CB122",7,FH,FS32X225K101EGG,2.2µF 100V,C_1210_3225Metric,SMD,PCBWay,C153036
2,"C3,C11,C13,C22,C23,C24,C25,C31,C32,C33,C34,C102,C103,C104,C120,C130,C202,C203,C204,C220,C230,C305,C325,C345,C365,CB54,CB124",27,Yageo,CC0603KRX7R9BB104,100nF,C_0603_1608Metric,SMD,PCBWay,C14663
3,C9,1,Taiyo Yuden,HMK212BC7105KGHTE,1µF 100V,C_0805_2012Metric,SMD,PCBWay,C385977
4,"C10,C18,C21,C101,C201",5,Samsung,CL21A106KAYNNNE,10µF 25V,C_0805_2012Metric,SMD,PCBWay,C15850
5,C12,1,Samsung,CL10B102KB8NNNC,1nF,C_0603_1608Metric,SMD,PCBWay,C1588
6,"C14,C30",2,Samsung,CL10A105KB8NNNC,1µF 50V,C_0603_1608Metric,SMD,PCBWay,C15849
7,C15,1,Lelon,RV100V47M8X10,47µF 100V,CP_Elec_8x10,SMD,PCBWay,C48935391
8,C17,1,Lelon,ERA10V2200M10X16,2200µF 10V,CP_Radial_D10.0mm_P5.00mm,THT,hand (William),C49256788
9,"C300,C301,C302,C320,C321,C322,C340,C341,C342,C360,C361,C362",12,FH,0603B103K101NT,10nF 100V,C_0603_1608Metric,SMD,PCBWay,C43253
10,"CB53,CB123",2,FH,0603B104K101NT,100nF 100V,C_0603_1608Metric,SMD,PCBWay,C88219
11,CB55,1,FH,0603B822K500NT,8.2nF,C_0603_1608Metric,SMD,PCBWay,C1322360
12,"CB56,CB126",2,Yageo,CC0603JRNPO9BN820,82pF C0G,C_0603_1608Metric,SMD,PCBWay,C107056
13,"CB57,CB58,CB59",3,Murata,GRM32ER71A476KE15L,47µF 10V,C_1210_3225Metric,SMD,PCBWay,C84494
14,CB125,1,Yageo,CC0603KRX7R9BB153,15nF,C_0603_1608Metric,SMD,PCBWay,C107076
15,"CB127,CB128,CB129",3,Samsung,CL32A226KAJNNNE,22µF 25V,C_1210_3225Metric,SMD,PCBWay,C52306
16,D1,1,Littelfuse,SMCJ48CA,SMCJ48CA,D_SMC,SMD,PCBWay,C151287
17,"D2,D12",2,Changjiang,BZT52C12,BZT52C12,D_SOD-123,SMD,PCBWay,C43491
18,"D3,D8",2,MDD,SS510C,SS510C,D_SMC,SMD,PCBWay,C19229
19,D9,1,TI,LM4040A25IDBZR,LM4040A25,SOT-23,SMD,PCBWay,C9421
20,D10,1,Hubei KENTO,KT-0603R,CHOP,LED_0603_1608Metric,SMD,PCBWay,C2286
21,D11,1,Hubei KENTO,KT-0603R,BUS LIVE,LED_0603_1608Metric,SMD,PCBWay,C2286
22,D13,1,Everlight,19-217/GHC-YR1S2/3T,5V,LED_0603_1608Metric,SMD,PCBWay,C72043
23,D14,1,MDD,SS34,SS34,D_SMA,SMD,PCBWay,C8678
24,"D16,D101,D201",3,Changjiang,B5819W,B5819W,D_SOD-123,SMD,PCBWay,C8598
25,D19,1,onsemi,NUP2105LT1G,NUP2105L,SOT-23,SMD,PCBWay,C14486
26,D20,1,onsemi,ESD5Z3.3T1G,ESD5Z3.3,D_SOD-523,SMD,PCBWay,C397781
27,D21,1,MDD,S1M,S1M,D_SMA,SMD,PCBWay,C2128
28,"D22,D23,D300,D301,D302,D320,D321,D322,D340,D341,D342,D360,D361,D362",14,Nexperia,"BAT54S,215",BAT54S,SOT-23,SMD,PCBWay,C47546
29,"DB5,DB12",2,Diodes Inc,B560C-13-F,B560C,D_SMC,SMD,PCBWay,C85100
30,J1,1,JST,B5P-VH(LF)(SN),PUISSANCE,JST_VH_B5P-VH_1x05_P3.96mm_Vertical,THT,hand (William),
31,J2,1,JST,B2B-XH-A(LF)(SN),SHUNT KELVIN,JST_XH_B2B-XH-A_1x02_P2.50mm_Vertical,THT,hand (William),C158012
32,J8,1,JST,B2B-XH-A(LF)(SN),FAN 12V,JST_XH_B2B-XH-A_1x02_P2.50mm_Vertical,THT,hand (William),C158012
33,J9,1,JST,B3B-XH-A(LF)(SN),CAN PC,JST_XH_B3B-XH-A_1x03_P2.50mm_Vertical,THT,hand (William),C144394
34,J10,1,JST,B2B-XH-A(LF)(SN),ARU /SAFE (NF),JST_XH_B2B-XH-A_1x02_P2.50mm_Vertical,THT,hand (William),C158012
35,J11,1,JST,B2B-XH-A(LF)(SN),ARU BOBINE (NF),JST_XH_B2B-XH-A_1x02_P2.50mm_Vertical,THT,hand (William),C158012
36,J13,1,JST,B2B-XH-A(LF)(SN),BOBINE CONTACTEUR,JST_XH_B2B-XH-A_1x02_P2.50mm_Vertical,THT,hand (William),C158012
37,J14,1,generic,1x10 female header 2.54 mm,IMU BNO085,PinSocket_1x10_P2.54mm_Vertical,THT,hand (William),
38,J15,1,JST,SM04B-GHS-TB(LF)(SN),BMS,JST_GH_SM04B-GHS-TB_1x04-1MP_P1.25mm_Horizontal,SMD,PCBWay,C189895
39,JC1,1,JST,B6B-XH-A(LF)(SN),COMMANDE AV_G,JST_XH_B6B-XH-A_1x06_P2.50mm_Vertical,THT,hand (William),C157992
40,JC2,1,JST,B6B-XH-A(LF)(SN),COMMANDE AV_D,JST_XH_B6B-XH-A_1x06_P2.50mm_Vertical,THT,hand (William),C157992
41,JC3,1,JST,B6B-XH-A(LF)(SN),COMMANDE AR_G,JST_XH_B6B-XH-A_1x06_P2.50mm_Vertical,THT,hand (William),C157992
42,JC4,1,JST,B6B-XH-A(LF)(SN),COMMANDE AR_D,JST_XH_B6B-XH-A_1x06_P2.50mm_Vertical,THT,hand (William),C157992
43,JD1,1,JST,B5B-XH-A(LF)(SN),HALL VARIATEUR AV_G,JST_XH_B5B-XH-A_1x05_P2.50mm_Vertical,THT,hand (William),C157991
44,JD2,1,JST,B5B-XH-A(LF)(SN),HALL VARIATEUR AV_D,JST_XH_B5B-XH-A_1x05_P2.50mm_Vertical,THT,hand (William),C157991
45,JD3,1,JST,B5B-XH-A(LF)(SN),HALL VARIATEUR AR_G,JST_XH_B5B-XH-A_1x05_P2.50mm_Vertical,THT,hand (William),C157991
46,JD4,1,JST,B5B-XH-A(LF)(SN),HALL VARIATEUR AR_D,JST_XH_B5B-XH-A_1x05_P2.50mm_Vertical,THT,hand (William),C157991
47,JM1,1,JST,B5B-XH-A(LF)(SN),HALL MOTEUR AV_G,JST_XH_B5B-XH-A_1x05_P2.50mm_Vertical,THT,hand (William),C157991
48,JM2,1,JST,B5B-XH-A(LF)(SN),HALL MOTEUR AV_D,JST_XH_B5B-XH-A_1x05_P2.50mm_Vertical,THT,hand (William),C157991
49,JM3,1,JST,B5B-XH-A(LF)(SN),HALL MOTEUR AR_G,JST_XH_B5B-XH-A_1x05_P2.50mm_Vertical,THT,hand (William),C157991
50,JM4,1,JST,B5B-XH-A(LF)(SN),HALL MOTEUR AR_D,JST_XH_B5B-XH-A_1x05_P2.50mm_Vertical,THT,hand (William),C157991
51,JP1,1,generic,1x3 pin header 2.54 mm + 1 jumper shunt,BOBINE 12V|BAT,PinHeader_1x03_P2.54mm_Vertical,THT,hand (William),
52,LB5,1,Bourns,SRP1265A-150M,15µH,L_TaiTech_TMPC1265_13.5x12.5mm,SMD,PCBWay,C189912
53,LB12,1,Cyntec,MDA1365-330M,33µH,L_TaiTech_TMPC1265_13.5x12.5mm,SMD,PCBWay,C2847586
54,"Q3,Q6",2,MCC,SUD50P10-43L-TP,SUD50P10-43L,TO-252-2,SMD,PCBWay,C41408040
55,Q4,1,Changjiang,MMBT5551,MMBT5551,SOT-23,SMD,PCBWay,C2145
56,"Q5,Q10",2,Infineon,IRL540NPBF,IRL540N,TO-220-3_Vertical,THT,hand (William),
57,"Q8,Q9,Q120,Q121,Q122,Q130,Q131,Q132,Q220,Q221,Q222,Q230,Q231,Q232",14,AOS,AO3400A,AO3400A,SOT-23,SMD,PCBWay,C20917
58,"R1,R2,R19,R29",4,UNI-ROYAL,0603WAF100JT5E,10Ω,R_0603_1608Metric,SMD,PCBWay,C22859
59,"R3,R21,R22,R28,R42,R49,R51,R56,R57,R61,R66,R101,R105,R109,R124,R134,R201,R205,R209,R224,R234",21,UNI-ROYAL,0603WAF1002T5E,10k,R_0603_1608Metric,SMD,PCBWay,C25804
60,R4,1,UNI-ROYAL,0603WAF2202T5E,22k,R_0603_1608Metric,SMD,PCBWay,C31850
61,"R5,R33",2,UNI-ROYAL,0603WAF4701T5E,4.7k,R_0603_1608Metric,SMD,PCBWay,C23162
62,"R6,R30,R31,R35,R45,R46,R47,R64,R103,R106,R110,R120,R121,R122,R130,R131,R132,R203,R206,R210,R220,R221,R222,R230,R231,R232",26,UNI-ROYAL,0603WAF1003T5E,100k,R_0603_1608Metric,SMD,PCBWay,C25803
63,R7,1,Yageo,SQP500JB-10R,10Ω 5W,R_Axial_Power_L25.0mm_W9.0mm_P10.16mm_Vertical,THT,hand (William),
64,R20,1,Yageo,AC0603FR-0793K1L,93.1k,R_0603_1608Metric,SMD,PCBWay,C228101
65,"R23,R24",2,Viking,AR03BTCX4992,49.9k 0.1%,R_0603_1608Metric,SMD,PCBWay,C2828622
66,R25,1,Viking,TD03G6191BT,6.19k 0.1%,R_0603_1608Metric,SMD,PCBWay,C667011
67,R26,1,UNI-ROYAL,0603WAF0000T5E,0R,R_0603_1608Metric,SMD,PCBWay,C21189
68,R27,1,UNI-ROYAL,0603WAF1694T5E,1.69M,R_0603_1608Metric,SMD,PCBWay,C247054
69,R32,1,UNI-ROYAL,0603WAF3302T5E,33k,R_0603_1608Metric,SMD,PCBWay,C4216
70,R34,1,Yageo,RC1206FR-0722KL,22k,R_1206_3216Metric,SMD,PCBWay,C114942
71,"R36,R55,R59,R65",4,UNI-ROYAL,0603WAF1001T5E,1k,R_0603_1608Metric,SMD,PCBWay,C21190
72,"R37,R38,R39,R40",4,UNI-ROYAL,1206W4F2200T5E,220Ω,R_1206_3216Metric,SMD,PCBWay,C17958
73,"R43,R44,R300,R301,R303,R304,R306,R307,R320,R321,R323,R324,R326,R327,R340,R341,R343,R344,R346,R347,R360,R361,R363,R364,R366,R367",26,UNI-ROYAL,0603WAF2201T5E,2.2k,R_0603_1608Metric,SMD,PCBWay,C4190
74,"R48,R50,RB53,RB123",4,UNI-ROYAL,0603WAF2433T5E,243k,R_0603_1608Metric,SMD,PCBWay,C23351
75,R52,1,UNI-ROYAL,0603WAF1200T5E,120Ω,R_0603_1608Metric,SMD,PCBWay,C22787
76,R60,1,UNI-ROYAL,0603WAF5231T5E,5.23k,R_0603_1608Metric,SMD,PCBWay,C23068
77,"R62,R63,R68,R123,R133,R223,R233",7,UNI-ROYAL,0603WAF1000T5E,100Ω,R_0603_1608Metric,SMD,PCBWay,C22775
78,R67,1,UNI-ROYAL,0603WAF2202T5E,22k,R_0603_1608Metric,SMD,DNP (do not place),C31850
79,"R102,R202",2,UNI-ROYAL,0603WAF4702T5E,47k,R_0603_1608Metric,SMD,PCBWay,C25819
80,"R104,R108,R204,R208",4,UNI-ROYAL,0603WAF6801T5E,6.8k,R_0603_1608Metric,SMD,PCBWay,C23212
81,"RB51,RB121",2,Yageo,AA0603FR-071M18L,1.18M,R_0603_1608Metric,SMD,PCBWay,C4072929
82,"RB52,RB122",2,UNI-ROYAL,0603WAF5902T5E,59k,R_0603_1608Metric,SMD,PCBWay,C23085
83,RB54,1,UNI-ROYAL,0603WAF5362T5E,53.6k,R_0603_1608Metric,SMD,PCBWay,C23074
84,"RB55,RB125",2,UNI-ROYAL,0603WAF1022T5E,10.2k,R_0603_1608Metric,SMD,PCBWay,C22772
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

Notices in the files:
README.md:
Licence: Apache 2.0
Hardware: CERN OHL S v2
hardware/pcb/motor_interface/kicad/motor_interface.kicad_sch:
Retriever, open hardware (CERN-OHL-S-2.0)
